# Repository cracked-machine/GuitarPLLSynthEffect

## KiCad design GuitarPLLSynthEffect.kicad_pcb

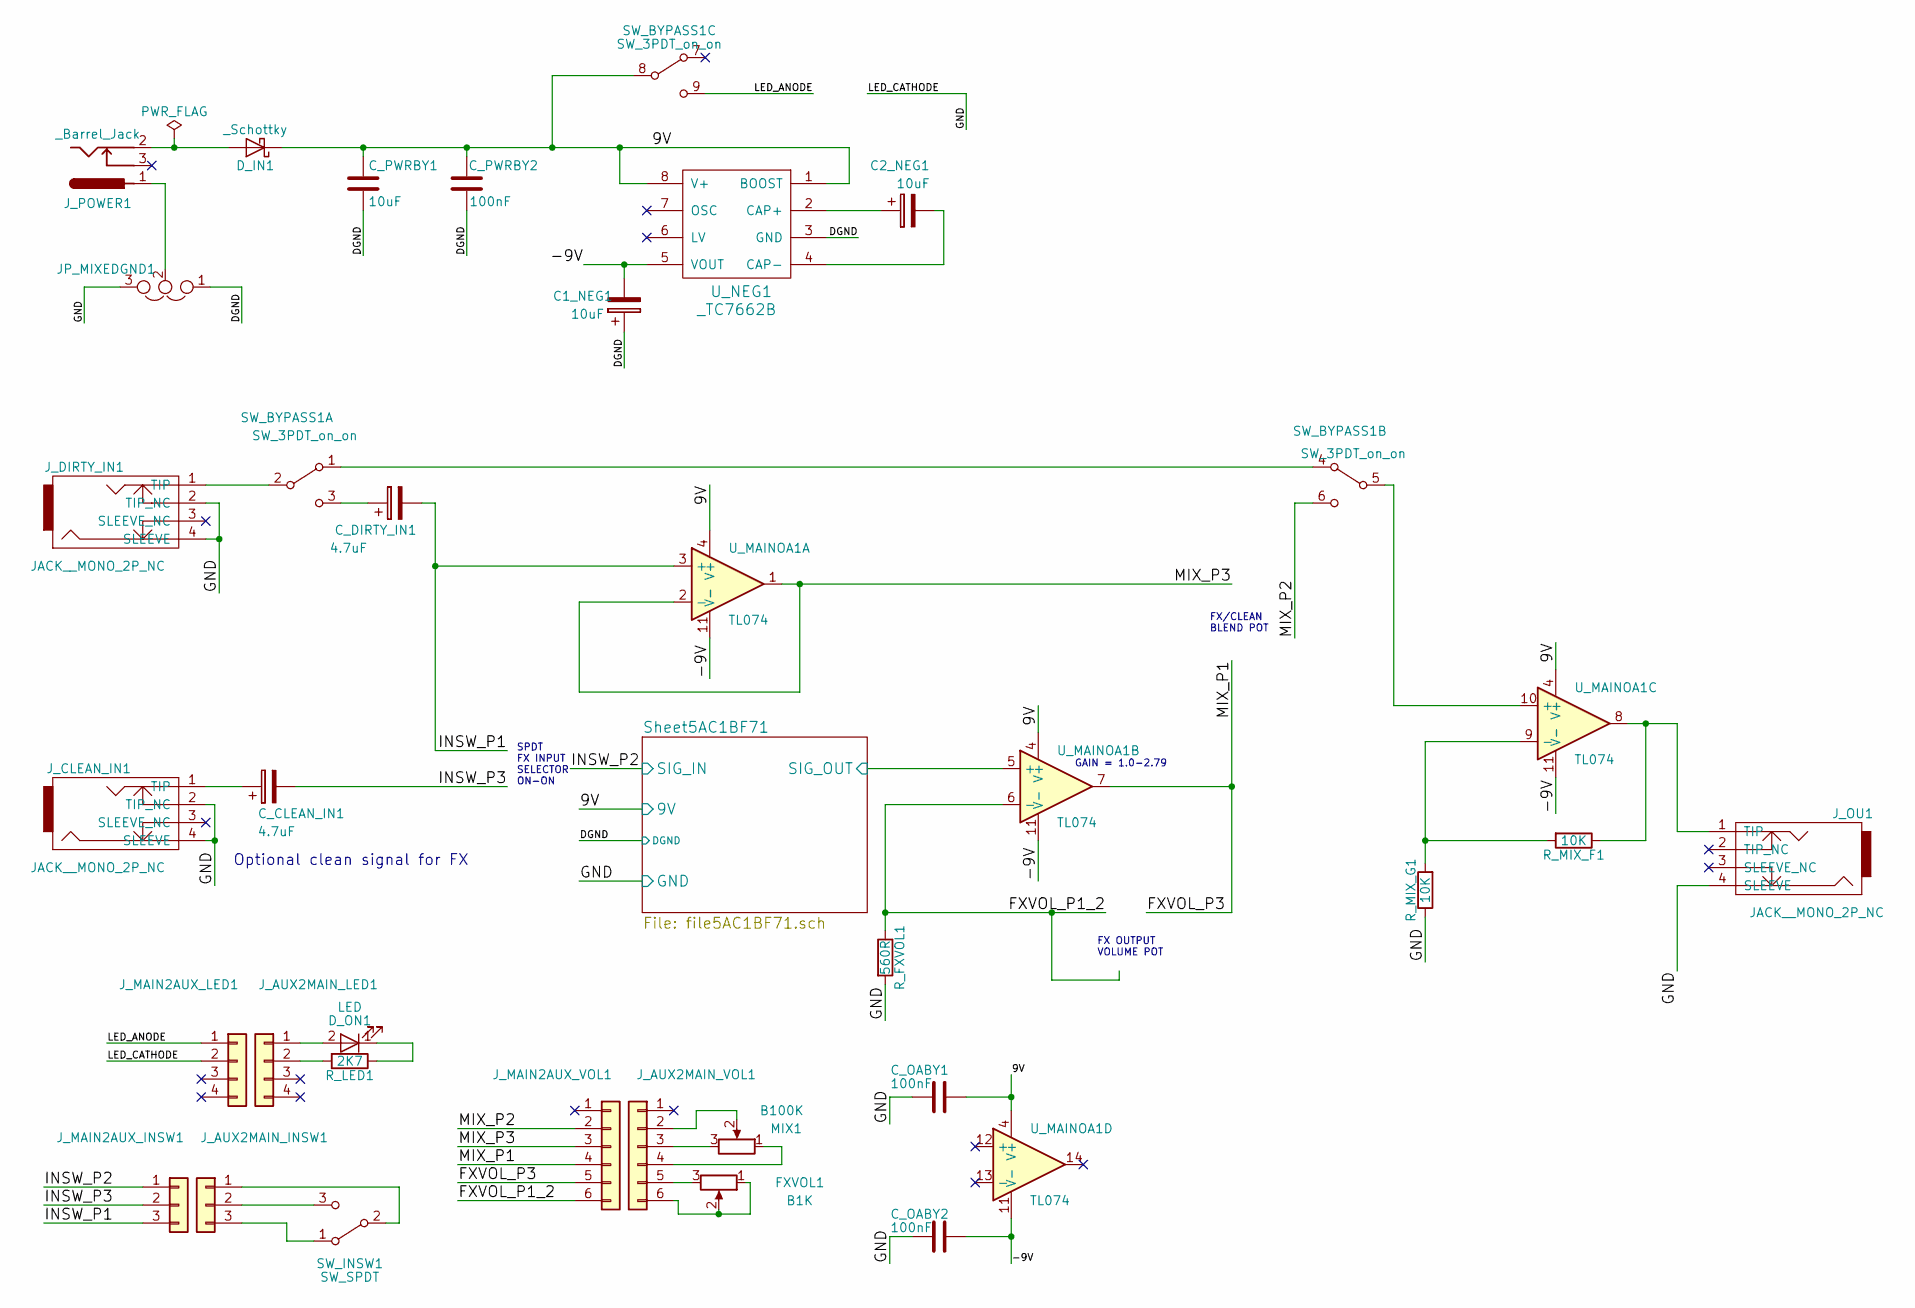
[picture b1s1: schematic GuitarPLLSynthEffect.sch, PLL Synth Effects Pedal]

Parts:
C1_NEG1, C2_NEG1: 10uF; CP_Elec_4x5.3
C_CLEAN_IN1: 4.7uF; C_0805_HandSoldering
C_DIRTY_IN1: 4.7uF; C_0805_HandSoldering
C_OABY1, C_OABY2: 100nF; C_0805_HandSoldering
C_PWRBY1: 10uF; CP_Elec_4x5.3
C_PWRBY2: 100nF; C_0805_HandSoldering
D_IN1: _Schottky; D_SOD-123F
D_ON1: LED; LED_D5.0mm
FXVOL1: B1K; Potentiometer_Bourns_PTV09A-1_Horizontal
JP_MIXEDGND1: Jumper_NC_Dual; NetTie-II_Connected_SMD
J_AUX2MAIN_INSW1: Conn_01x03; Pin_Header_Straight_1x03_Pitch2.54mm
J_AUX2MAIN_LED1: Conn_01x04; Pin_Header_Straight_1x04_Pitch2.54mm
J_AUX2MAIN_VOL1: Conn_01x06; Pin_Header_Straight_1x06_Pitch2.54mm
J_CLEAN_IN1: JACK__MONO_2P_NC; JackSocket_Mono_PCB
J_DIRTY_IN1: JACK__MONO_2P_NC; JackSocket_Mono_PCB
J_MAIN2AUX_INSW1: Conn_01x03; Pin_Header_Straight_1x03_Pitch2.54mm
J_MAIN2AUX_LED1: Conn_01x04; Pin_Header_Straight_1x04_Pitch2.54mm
J_MAIN2AUX_VOL1: Conn_01x06; Pin_Header_Straight_1x06_Pitch2.54mm
J_OU1: JACK__MONO_2P_NC; JackSocket_Mono_PCB
J_POWER1: _Barrel_Jack; BARREL_JACK
MIX1: B100K; Potentiometer_Bourns_PTV09A-1_Horizontal
R_FXVOL1: 560R; R_0805_HandSoldering
R_LED1: 2K7; R_0805_HandSoldering
R_MIX_F1: 10K; R_0805_HandSoldering
R_MIX_G1: 10K; R_0805_HandSoldering
SW_BYPASS1: SW_3PDT_on_on; SW_3PDT_W18MM_L17.3MM_P5.3MM_D2MM_PCBPin
SW_INSW1: SW_SPDT; SW_SPDT_W6.86MM_L12.7MM_P4.8MM_D2MM
U_MAINOA1: TL074; SOIC-14_N
U_NEG1: _TC7662B; SOIC-8-N

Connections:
/9V: C_OABY1.1, C_PWRBY1.1, C_PWRBY2.2, D_IN1.1 (K), SW_BYPASS1.8 (B), U_MAINOA1.4 (V+), U_NEG1.1 (BOOST), U_NEG1.8 (V+); also elsewhere on the board
/-9V: C1_NEG1.2, C_OABY2.1, U_MAINOA1.11 (V-), U_NEG1.5 (VOUT)
/DGND: C1_NEG1.1, C_PWRBY1.2, C_PWRBY2.1, JP_MIXEDGND1.1, U_NEG1.3 (GND); also elsewhere on the board
/FXVOL_P1_2: J_MAIN2AUX_VOL1.6, R_FXVOL1.1, U_MAINOA1.6 (-)
/FXVOL_P3: J_MAIN2AUX_VOL1.4, J_MAIN2AUX_VOL1.5, U_MAINOA1.7
/GND: C_OABY1.2, C_OABY2.2, JP_MIXEDGND1.3, J_CLEAN_IN1.2 (TIP_NC), J_CLEAN_IN1.4 (SLEEVE), J_DIRTY_IN1.2 (TIP_NC), J_DIRTY_IN1.4 (SLEEVE), J_MAIN2AUX_LED1.2, J_OU1.4 (SLEEVE), R_FXVOL1.2, R_MIX_G1.1; also elsewhere on the board
/INSW_P1: C_DIRTY_IN1.2, J_MAIN2AUX_INSW1.3, U_MAINOA1.3 (+)
/INSW_P2: J_MAIN2AUX_INSW1.1; also elsewhere on the board
/INSW_P3: C_CLEAN_IN1.2, J_MAIN2AUX_INSW1.2
/LED_ANODE: J_MAIN2AUX_LED1.1, SW_BYPASS1.9 (C)
/MIX_P2: J_MAIN2AUX_VOL1.2, SW_BYPASS1.6 (C)
/MIX_P3: J_MAIN2AUX_VOL1.3, U_MAINOA1.1, U_MAINOA1.2 (-)
/Sheet5AC1BF71/SIG_OUT: U_MAINOA1.5 (+); also elsewhere on the board
unnamed: C2_NEG1.1, U_NEG1.2 (CAP+)
unnamed: C2_NEG1.2, U_NEG1.4 (CAP-)
unnamed: C_CLEAN_IN1.1, J_CLEAN_IN1.1 (TIP)
unnamed: C_DIRTY_IN1.1, SW_BYPASS1.3 (C)
unnamed: D_IN1.2 (A), J_POWER1.2
unnamed: D_ON1.1 (K), R_LED1.1
unnamed: D_ON1.2 (A), J_AUX2MAIN_LED1.1
unnamed: FXVOL1.1, FXVOL1.2, J_AUX2MAIN_VOL1.6
unnamed: FXVOL1.3, J_AUX2MAIN_VOL1.5
unnamed: JP_MIXEDGND1.2, J_POWER1.1
unnamed: J_AUX2MAIN_INSW1.1, SW_INSW1.2 (B)
unnamed: J_AUX2MAIN_INSW1.2, SW_INSW1.3 (C)
unnamed: J_AUX2MAIN_INSW1.3, SW_INSW1.1 (A)
unnamed: J_AUX2MAIN_LED1.2, R_LED1.2
unnamed: J_AUX2MAIN_VOL1.2, MIX1.2
unnamed: J_AUX2MAIN_VOL1.3, MIX1.3
unnamed: J_AUX2MAIN_VOL1.4, MIX1.1
unnamed: J_DIRTY_IN1.1 (TIP), SW_BYPASS1.2 (B)
unnamed: J_OU1.1 (TIP), R_MIX_F1.1, U_MAINOA1.8
unnamed: R_MIX_F1.2, R_MIX_G1.2, U_MAINOA1.9 (-)
unnamed: SW_BYPASS1.1 (A), SW_BYPASS1.4 (A)
unnamed: SW_BYPASS1.5 (B), U_MAINOA1.10 (+)

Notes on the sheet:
GAIN = 1.0-2.79
Optional clean signal for FX
SPDT FX INPUT SELECTOR ON-ON
FX OUTPUT VOLUME POT
FX/CLEAN BLEND POT

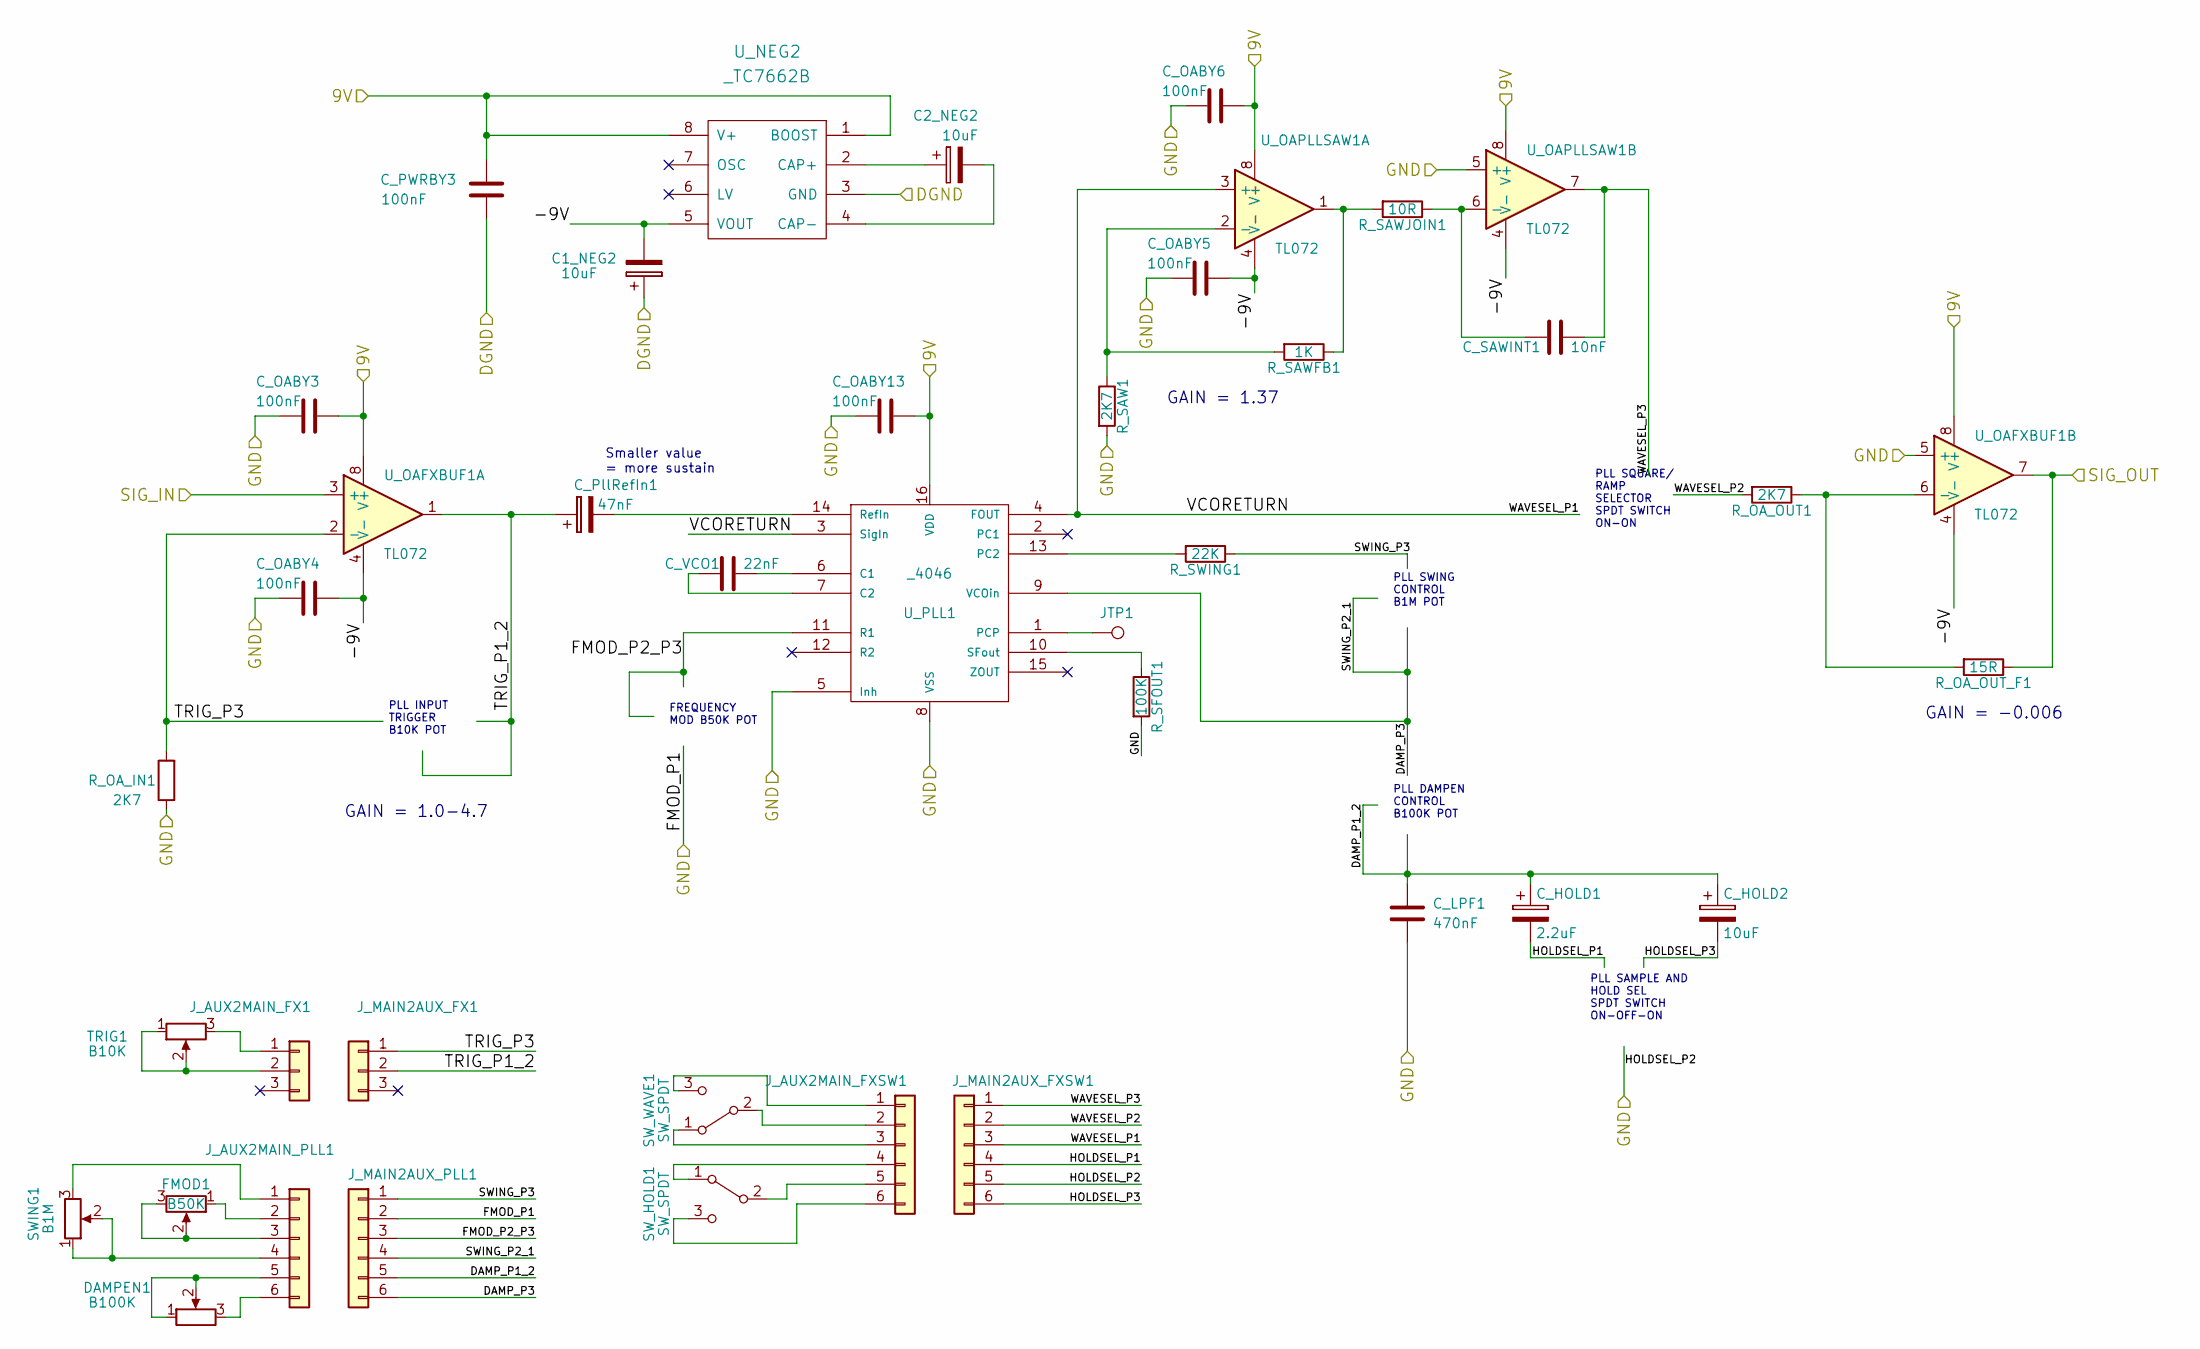
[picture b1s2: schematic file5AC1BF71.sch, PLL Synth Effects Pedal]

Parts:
C1_NEG2, C2_NEG2: 10uF; CP_Elec_4x5.3
C_HOLD1: 2.2uF; C_0805_HandSoldering
C_HOLD2: 10uF; C_0805_HandSoldering
C_LPF1: 470nF; C_0805_HandSoldering
C_OABY3, C_OABY4, C_OABY5, C_OABY6, C_OABY13: 100nF; C_0805_HandSoldering
C_PWRBY3: 100nF; C_0805_HandSoldering
C_PllRefIn1: 47nF; C_0805_HandSoldering
C_SAWINT1: 10nF; C_0805_HandSoldering
C_VCO1: 22nF; C_0805_HandSoldering
DAMPEN1: B100K; Potentiometer_Bourns_PTV09A-1_Horizontal
FMOD1: B50K; Potentiometer_Bourns_PTV09A-1_Horizontal
JTP1: TEST_1P; Measurement_Point_Round-SMD-Pad_Small
J_AUX2MAIN_FX1: Conn_01x03; Pin_Header_Straight_1x03_Pitch2.54mm
J_AUX2MAIN_FXSW1, J_AUX2MAIN_PLL1: Conn_01x06; Pin_Header_Straight_1x06_Pitch2.54mm
J_MAIN2AUX_FX1: Conn_01x03; Pin_Header_Straight_1x03_Pitch2.54mm
J_MAIN2AUX_FXSW1, J_MAIN2AUX_PLL1: Conn_01x06; Pin_Header_Straight_1x06_Pitch2.54mm
R_OA_IN1: 2K7; R_0805_HandSoldering
R_OA_OUT1: 2K7; R_0805_HandSoldering
R_OA_OUT_F1: 15R; R_0805_HandSoldering
R_SAW1: 2K7; R_0805_HandSoldering
R_SAWFB1: 1K; R_0805_HandSoldering
R_SAWJOIN1: 10R; R_0805_HandSoldering
R_SFOUT1: 100K; R_0805_HandSoldering
R_SWING1: 22K; R_0805_HandSoldering
SWING1: B1M; Potentiometer_Bourns_PTV09A-1_Horizontal
SW_HOLD1: SW_SPDT; SW_SPDT_W6.86MM_L12.7MM_P4.8MM_D2MM
SW_WAVE1: SW_SPDT; SW_SPDT_W6.86MM_L12.7MM_P4.8MM_D2MM
TRIG1: B10K; Potentiometer_Bourns_PTV09A-1_Horizontal
U_NEG2: _TC7662B; SOIC-8-N
U_OAFXBUF1: TL072; SOIC-8-N
U_OAPLLSAW1: TL072; SOIC-8-N
U_PLL1: _4046; SO-16-N++

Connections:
/9V: C_OABY3.1, C_OABY6.1, C_OABY13.1, C_PWRBY3.2, U_NEG2.1 (BOOST), U_NEG2.8 (V+), U_OAFXBUF1.8 (V+), U_OAPLLSAW1.8 (V+), U_PLL1.16 (VDD); also elsewhere on the board
/DGND: C1_NEG2.1, C_PWRBY3.1, U_NEG2.3 (GND); also elsewhere on the board
/GND: C_LPF1.2, C_OABY3.2, C_OABY4.2, C_OABY5.2, C_OABY6.2, C_OABY13.2, J_MAIN2AUX_FXSW1.5, J_MAIN2AUX_PLL1.2, R_OA_IN1.1, R_SAW1.2, R_SFOUT1.2, U_OAFXBUF1.5 (+), U_OAPLLSAW1.5 (+), U_PLL1.5 (Inh), U_PLL1.8 (VSS); also elsewhere on the board
/INSW_P2: U_OAFXBUF1.3 (+); also elsewhere on the board
/Sheet5AC1BF71/-9V: C1_NEG2.2, C_OABY4.1, C_OABY5.1, U_NEG2.5 (VOUT), U_OAFXBUF1.4 (V-), U_OAPLLSAW1.4 (V-)
/Sheet5AC1BF71/DAMP_P1_2: C_HOLD1.1, C_HOLD2.1, C_LPF1.1, J_MAIN2AUX_PLL1.5
/Sheet5AC1BF71/DAMP_P3: J_MAIN2AUX_PLL1.4, J_MAIN2AUX_PLL1.6, U_PLL1.9 (VCOin)
/Sheet5AC1BF71/FMOD_P2_P3: J_MAIN2AUX_PLL1.3, U_PLL1.11 (R1)
/Sheet5AC1BF71/HOLDSEL_P1: C_HOLD1.2, J_MAIN2AUX_FXSW1.4
/Sheet5AC1BF71/HOLDSEL_P3: C_HOLD2.2, J_MAIN2AUX_FXSW1.6
/Sheet5AC1BF71/SIG_OUT: R_OA_OUT_F1.1, U_OAFXBUF1.7; also elsewhere on the board
/Sheet5AC1BF71/SWING_P3: J_MAIN2AUX_PLL1.1, R_SWING1.1
/Sheet5AC1BF71/TRIG_P1_2: C_PllRefIn1.1, J_MAIN2AUX_FX1.2, U_OAFXBUF1.1
/Sheet5AC1BF71/TRIG_P3: J_MAIN2AUX_FX1.1, R_OA_IN1.2, U_OAFXBUF1.2 (-)
/Sheet5AC1BF71/VCORETURN: J_MAIN2AUX_FXSW1.3, U_OAPLLSAW1.3 (+), U_PLL1.3 (SigIn), U_PLL1.4 (FOUT)
/Sheet5AC1BF71/WAVESEL_P2: J_MAIN2AUX_FXSW1.2, R_OA_OUT1.2
/Sheet5AC1BF71/WAVESEL_P3: C_SAWINT1.1, J_MAIN2AUX_FXSW1.1, U_OAPLLSAW1.7
unnamed: C2_NEG2.1, U_NEG2.2 (CAP+)
unnamed: C2_NEG2.2, U_NEG2.4 (CAP-)
unnamed: C_PllRefIn1.2, U_PLL1.14 (RefIn)
unnamed: C_SAWINT1.2, R_SAWJOIN1.1, U_OAPLLSAW1.6 (-)
unnamed: C_VCO1.1, U_PLL1.6 (C1)
unnamed: C_VCO1.2, U_PLL1.7 (C2)
unnamed: DAMPEN1.1, DAMPEN1.2, J_AUX2MAIN_PLL1.5
unnamed: DAMPEN1.3, J_AUX2MAIN_PLL1.6
unnamed: FMOD1.1, J_AUX2MAIN_PLL1.2
unnamed: FMOD1.2, FMOD1.3, J_AUX2MAIN_PLL1.3
unnamed: JTP1.1, U_PLL1.1 (PCP)
unnamed: J_AUX2MAIN_FX1.1, TRIG1.3
unnamed: J_AUX2MAIN_FX1.2, TRIG1.1, TRIG1.2
unnamed: J_AUX2MAIN_FXSW1.1, SW_WAVE1.3 (C)
unnamed: J_AUX2MAIN_FXSW1.2, SW_WAVE1.2 (B)
unnamed: J_AUX2MAIN_FXSW1.3, SW_WAVE1.1 (A)
unnamed: J_AUX2MAIN_FXSW1.4, SW_HOLD1.1 (A)
unnamed: J_AUX2MAIN_FXSW1.5, SW_HOLD1.2 (B)
unnamed: J_AUX2MAIN_FXSW1.6, SW_HOLD1.3 (C)
unnamed: J_AUX2MAIN_PLL1.1, SWING1.3
unnamed: J_AUX2MAIN_PLL1.4, SWING1.1, SWING1.2
unnamed: R_OA_OUT1.1, R_OA_OUT_F1.2, U_OAFXBUF1.6 (-)
unnamed: R_SAW1.1, R_SAWFB1.2, U_OAPLLSAW1.2 (-)
unnamed: R_SAWFB1.1, R_SAWJOIN1.2, U_OAPLLSAW1.1
unnamed: R_SFOUT1.1, U_PLL1.10 (SFout)
unnamed: R_SWING1.2, U_PLL1.13 (PC2)

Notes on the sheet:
Smaller value = more sustain
GAIN = -0.006
GAIN = 1.0-4.7
GAIN = 1.37
PLL INPUT TRIGGER B10K POT
FREQUENCY MOD B50K POT
PLL SWING CONTROL B1M POT
PLL DAMPEN CONTROL B100K POT
PLL SAMPLE AND HOLD SEL SPDT SWITCH ON-OFF-ON
PLL SQUARE/ RAMP SELECTOR SPDT SWITCH ON-ON

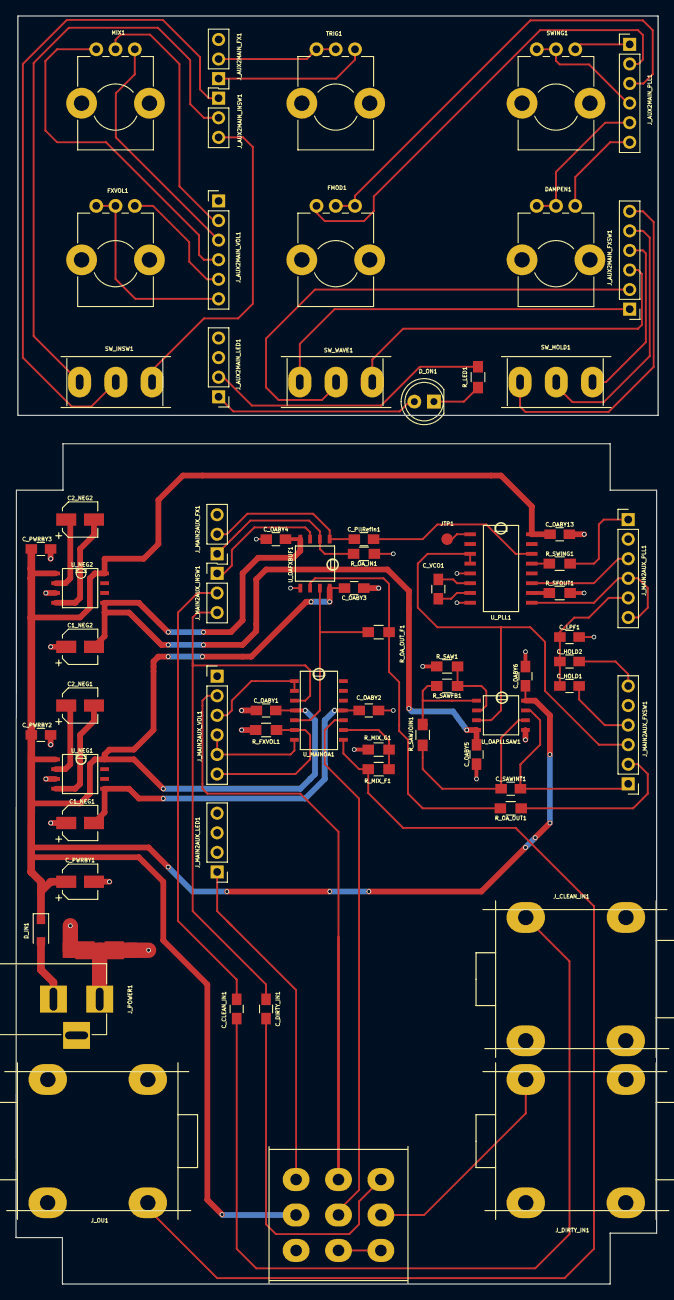
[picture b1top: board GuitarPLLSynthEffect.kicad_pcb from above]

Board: 2 copper layers, 83.3 x 164.5 mm, 70 parts (0 on the bottom side), 73 nets.

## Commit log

2018-03-29 First Commit
    - Added basic schematic
2018-03-30 Schematic design update
    - Added PLL controls
    - Added dual power supply (TC7662B)
    - Added Output buffer OpAmp
2018-03-30 Set theme jekyll-theme-slate
2018-03-30 Rename index.html to readme.md
2018-03-31 Schematic design update
    - Added fx trigger/gain control to OAFX_IN opamp
    - Added FM control to PLL
    - Added clean/fx summing opamp
2018-04-01 UPDATE
    ADDED FX OUPUT GAIN STAGE
    ADDED FX/CLEAN MIXER OPAMP (WITH SINGLE BLEND POT CONTROL)
2018-04-01 schematic design update
    Added saw wave
2018-04-02 schematic design update
    Added clean signal input and selector switch (dirty signal will always go to mixer)
2018-04-02 Final RevA Schematic
2018-04-03 Added board layout
2018-04-03 Board Design Update RevA
2018-04-03 Completed First Draft board Layout RevA
2018-04-04 Second draft PCB layout
2018-04-05 Corrections to board dimensions, adjusted layout to fit
2018-04-07 final layout
2018-04-07 Layout design corrections
2018-04-08 layout updates
2018-04-08 layout update
2018-05-02 Board Layout updates
    - Increased PLL footprint width
    - Separated FX TL074 into 2 TL072's.
2018-05-03 Board Layout redesign
2018-05-06 Board Redesign - RevB
    - Created seperate ground plane for DC-DC Converters
    - Re-routed the rest of the board.
2018-05-30 board correction
